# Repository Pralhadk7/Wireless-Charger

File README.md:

# Wireless-Charger
Wireless charger projects involve the development and implementation of technology that allows for the transfer of electrical energy from a power source to a device without the need for physical cables or connectors. These projects typically focus on creating efficient and convenient charging solutions for various electronic devices, such as smartphones, tablets, wearables, and more.

The core principle behind wireless charging is electromagnetic induction or resonance coupling. A wireless charger consists of two main components: a charging pad or station, which generates an electromagnetic field, and a receiver or receiver coil embedded in the device to be charged. When the receiver coil comes into close proximity with the charging pad, the electromagnetic field induces an electrical current in the receiver coil, which is then used to charge the device's battery.

Wireless charger projects aim to improve charging efficiency, increase charging distances, and enhance compatibility across different devices. Researchers and engineers work on optimizing the design and layout of the charging pad and receiver coil to maximize energy transfer and minimize energy loss. They also focus on developing advanced control algorithms and power management systems to ensure safe and efficient charging.

In recent years, wireless charger projects have seen significant advancements, with the introduction of technologies like Qi (pronounced "chee") wireless charging standard, which has become widely adopted in the industry. Qi-compatible chargers are capable of charging multiple devices simultaneously and offer convenient placement flexibility. Additionally, some projects explore innovative approaches like wireless charging through radio waves or even over longer distances using technologies like magnetic resonance or laser.

Overall, wireless charger projects strive to revolutionize the way we recharge our devices by eliminating the need for cumbersome cables and connectors, providing a convenient and clutter-free charging experience.

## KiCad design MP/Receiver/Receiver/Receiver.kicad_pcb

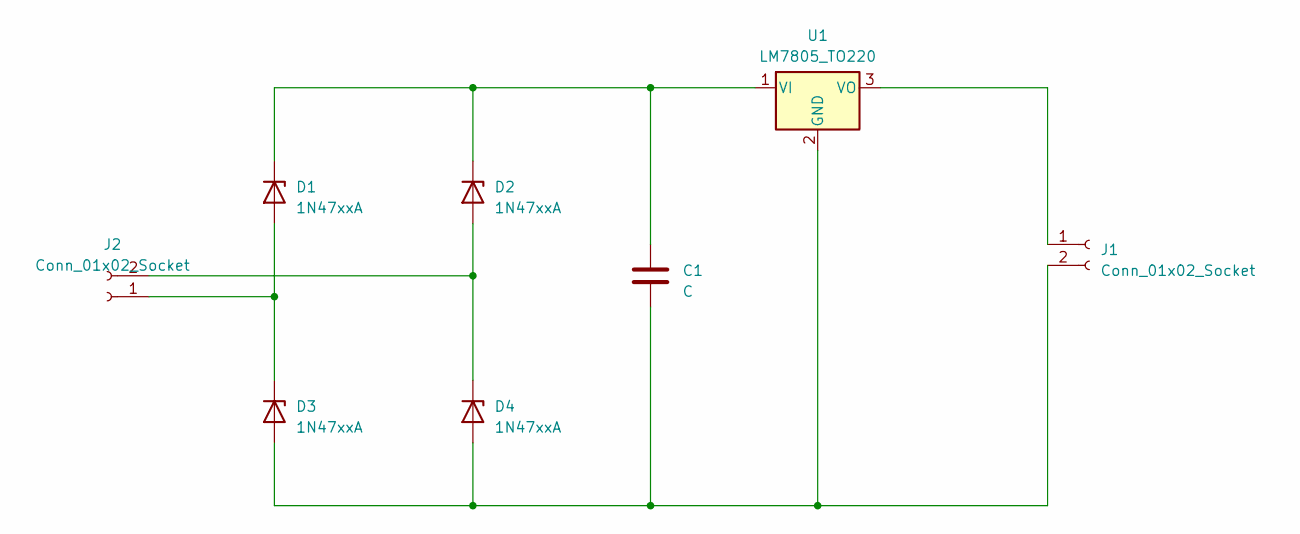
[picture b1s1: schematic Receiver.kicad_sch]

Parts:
C1: C; CP_Axial_L11.0mm_D6.0mm_P18.00mm_Horizontal
D1, D2, D3, D4: 1N47xxA; D_DO-41_SOD81_P10.16mm_Horizontal
J1, J2: Conn_01x02_Socket; Banana_Jack_2Pin
U1: LM7805_TO220; TO-220-3_Vertical

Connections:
unnamed: D1.2 (A), D3.1 (K), J2.1
unnamed: C1.1, D1.1 (K), D2.1 (K), U1.1 (VI)
unnamed: D2.2 (A), D4.1 (K), J2.2
unnamed: C1.2, D3.2 (A), D4.2 (A), J1.2, U1.2 (GND)
unnamed: J1.1, U1.3 (VO)

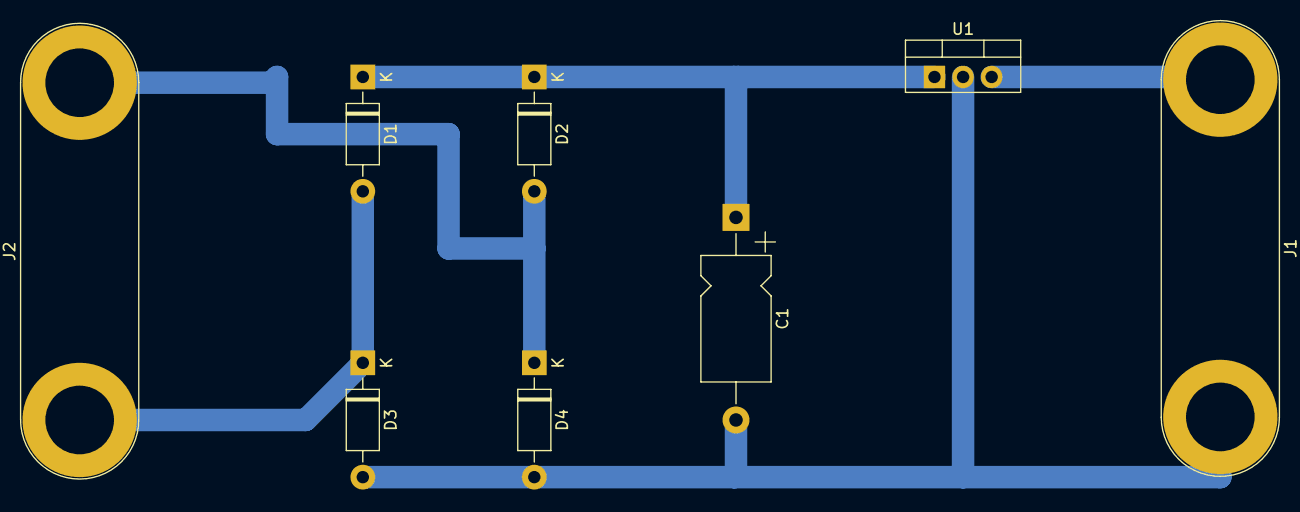
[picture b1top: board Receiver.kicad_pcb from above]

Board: 2 copper layers, 8 parts (0 on the bottom side), 5 nets.

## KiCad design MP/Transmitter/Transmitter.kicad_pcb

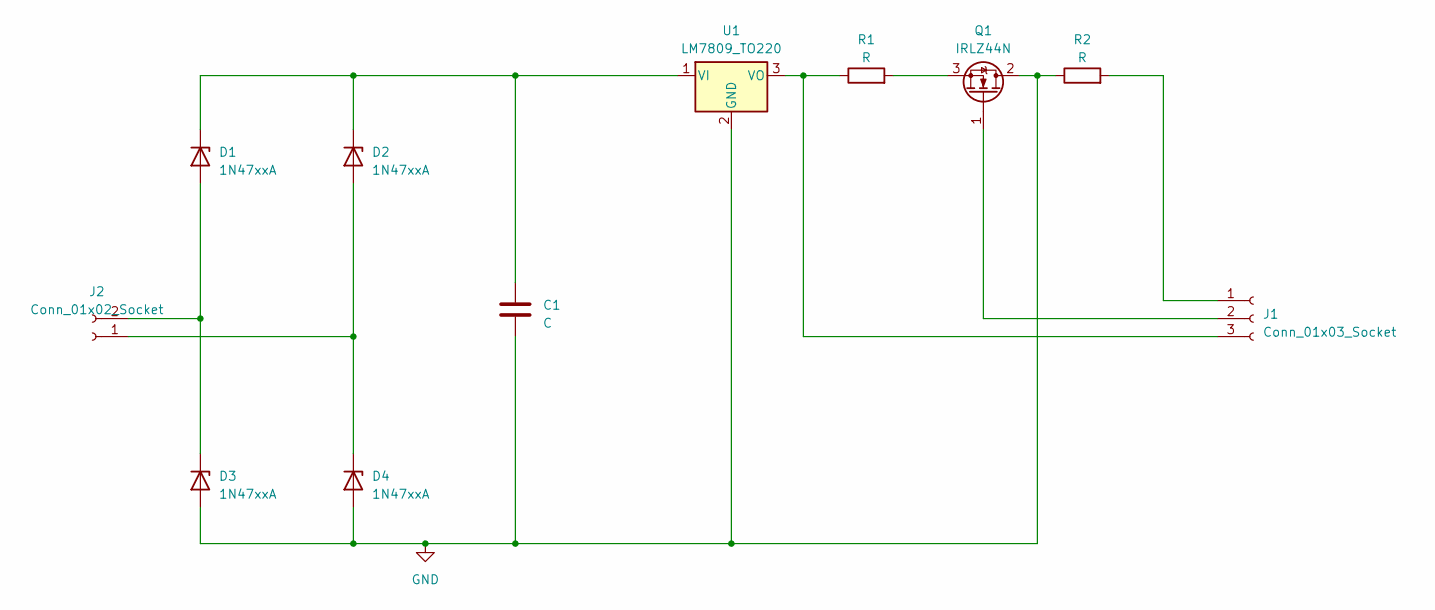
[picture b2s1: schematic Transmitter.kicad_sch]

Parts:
C1: C; CP_Axial_L18.0mm_D6.5mm_P25.00mm_Horizontal
D1, D2, D3, D4: 1N47xxA; D_DO-41_SOD81_P10.16mm_Horizontal
J1: Conn_01x03_Socket; Banana_Jack_3Pin
J2: Conn_01x02_Socket; Banana_Jack_2Pin
Q1: IRLZ44N; TO-220-3_Vertical
R1, R2: R; R_Axial_DIN0207_L6.3mm_D2.5mm_P15.24mm_Horizontal
U1: LM7809_TO220; TO-220-3_Vertical

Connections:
GND: C1.2, D3.2 (A), D4.2 (A), Q1.2 (D), R2.1, U1.2 (GND)
unnamed: D1.2 (A), D3.1 (K), J2.2
unnamed: C1.1, D1.1 (K), D2.1 (K), U1.1 (VI)
unnamed: D2.2 (A), D4.1 (K), J2.1
unnamed: J1.1, R2.2
unnamed: J1.2, Q1.1 (G)
unnamed: J1.3, R1.1, U1.3 (VO)
unnamed: Q1.3 (S), R1.2

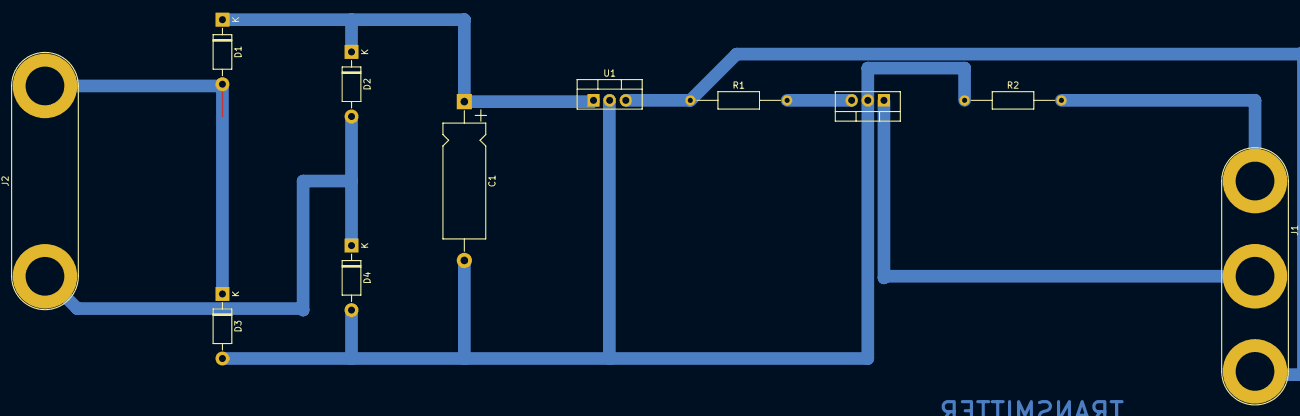
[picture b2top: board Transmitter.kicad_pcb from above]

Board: 2 copper layers, 11 parts (0 on the bottom side), 8 nets.
